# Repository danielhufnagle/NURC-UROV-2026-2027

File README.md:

# NURC-UROV-2026-2027
Electrical and Software for MATE UROV 2026-2027
well hello there

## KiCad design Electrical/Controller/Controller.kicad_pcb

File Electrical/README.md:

# Electrical

Place all PCB files here. Include both component and footprint libraries as well

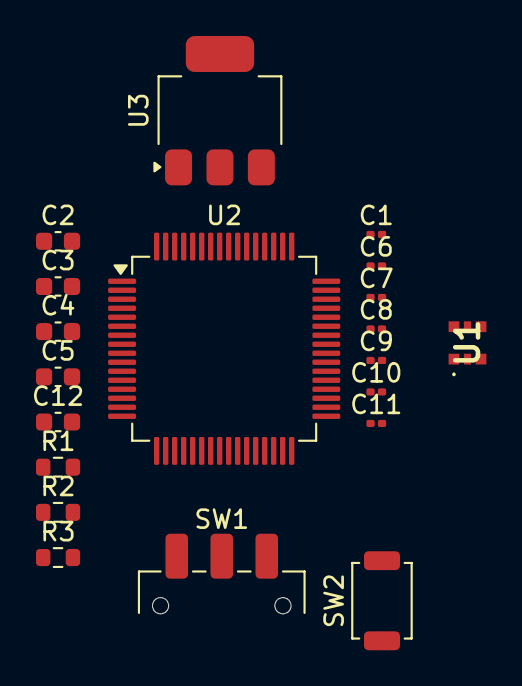
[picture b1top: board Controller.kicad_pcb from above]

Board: 2 copper layers, 20 parts (0 on the bottom side), 9 nets, no tracks yet.

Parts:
C1, C6, C7, C8, C9, C10, C11: 100nf; C_0201_0603Metric
C2, C3, C4: 10uf; C_0603_1608Metric
C5, C12: 100nf; C_0603_1608Metric
R1, R2, R3: 10k; R_0603_1608Metric
SW1: SW_SPDT; SW_SPDT_CK_JS102011SAQN
SW2: SW_SPST; SW_SPST_TS-1088-xR020
U1: 74LVC1G332; 74LVC1G332GW125
U2: STM32F446RETx; LQFP-64_10x10mm_P0.5mm
U3: AMS1117-3.3; SOT-223-3_TabPin2

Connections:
+5V: C4.1, U3.3 (VI)
/IsLeak: U1.4, U2.40 (PC9)
/LDO 3V3: C3.1, C6.1, C7.1, C8.1, C9.1, C10.1, C11.1, C12.2, R1.1, R3.1, U1.5 (VCC), U2.1 (VBAT), U2.13 (VDDA), U2.19 (VDD), U2.32 (VDD), U2.48 (VDD), U2.64 (VDD), U3.2 (VO)
GND: C1.2, C2.2, C3.2, C4.2, C5.1, C6.2, C7.2, C8.2, C9.2, C10.2, C11.2, C12.1, R2.2, SW2.1 (A), U1.2 (GND), U2.12 (VSSA), U2.18 (VSS), U2.31 (VSS), U2.47 (VSS), U2.63 (VSS), U3.1 (GND)
unnamed: R2.1, SW1.1 (A)
unnamed: C1.1, SW1.2 (B), U2.60 (BOOT0)
unnamed: R1.2, SW1.3 (C)
unnamed: C5.2, R3.2, SW2.2 (B), U2.7 (NRST)
unnamed: C2.1, U2.30 (VCAP_1)
